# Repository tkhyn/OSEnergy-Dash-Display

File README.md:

# OSEnergy Dash Display

#####A 2" Dash Display for the VSR Alternator Regulator, and other OSEnergy complaint devices.

The OSEnergy Dashboard Display is a combination of hardware and software and designed to provide  information  of your battery and its associated charging sources.  Usable with any OSEnergy compliant device (such as the [VSR Alternator Regulator](http://arduinoalternatorregulator.blogspot.com/) ), this simple gauge will monitor the communications bus providing you with real-time updates of any active devices.

<br><br>
###How to Purchase and Install
The OSEnergy-Dash-Display source code has been proofed on the PUT NAME HERE AS WELL AS LINK open xxxx.  You can purchase a preassembled version complete with firmware installed here: link-here.

The raw display is sold by this person:  [https://www.tindie.com/stores/geraldjust/](https://www.tindie.com/stores/geraldjust/#store-section-products) 

The addaptor board gbr files are in this GitHub, or you can order some from  [OSHPARK](https://oshpark.com/shared_projects/Y1xcmnih) 

Firmware is in this Github, program the display using an FTDI cable.

Insert Photo of finished device

<br><br>
###Usage:

Once installed and connected, the Dash Display will monitor the CAN communications bus looking for battery information as well as any chargers associated with that battery.  Up to 4x different batteries may be monitored at one time, as well as up to 10x different charging sources.  When 1st powered up the display will show a  'Searching' message; as battery information is found it will change the display to reflect the battery as well as any charging source associated with that battery.

The PUT NAME HERE display hardware has 3 touch-pad buttons along the lower edge of the OLED display.  Pressing the LEFT button will cycle between battery information and its associated charging sources.  Pressing the RIGHT button will cycle between different batteries in your system.  After a period of inactivity the display may darken.  You can awaken the dash display by pressing the CENTER button

<br>
###Information displayed
####The following battery information may be displayed:
- Battery Name / ID number
- Battery Voltage, Current, Temperature
- Battery SOC

<br><br><br>
####The following Charging Source information may be displayed:
- Voltage at charging source
- Current being delivered by charging source
- Temperature of charging source
- % capability of charging source presently be utilized.
- Charging mode

Note that not all information may be available, depending on the capabilities of the associated device(s) installed in your system.  For example, if you only have a VSR Alternator Regulator installed battery SOC will not be shown.  To see Battery SOC you will need to install something which actually tracks SOC over the long term, such as a proper Battery Monitor or BMS.

<br><br>
####VSR Alternator Regulator Configuration Hints and notes:
- The  [VSR Alternator Regulator](http://arduinoalternatorregulator.blogspot.com/) needs to be configured to explicitly tell it its current shunt is located AT the battery by using the $CCN: command (Providing it is located at the battery).  Otherwise current will be recognized on the Alternator screen instead of the Battery screen.
- Generation 3 of the VSR Alternator Regulator does not supply power via the CAT-5 cable.  You will need to connect the external power wires on the display.  Generation 3B and beyond have the ability to provide power to the CAN CAT-5 cable directly, and no addition power wiring is needed.
- Update the VSR Alternator Regulator firmware  to version 1.3.1 or greater to maximize the capability of the Dash Display.

<br><br>
####Source code notes:
Download and compile using the Arduino IDE.  Make sure to install the ATmega64M1 CPU type as well as the AVR_CAN and RV-C libraries:

https://github.com/thomasonw/ATmegaxxM1-C1
https://github.com/thomasonw/avr_can
https://github.com/thomasonw/RV-C

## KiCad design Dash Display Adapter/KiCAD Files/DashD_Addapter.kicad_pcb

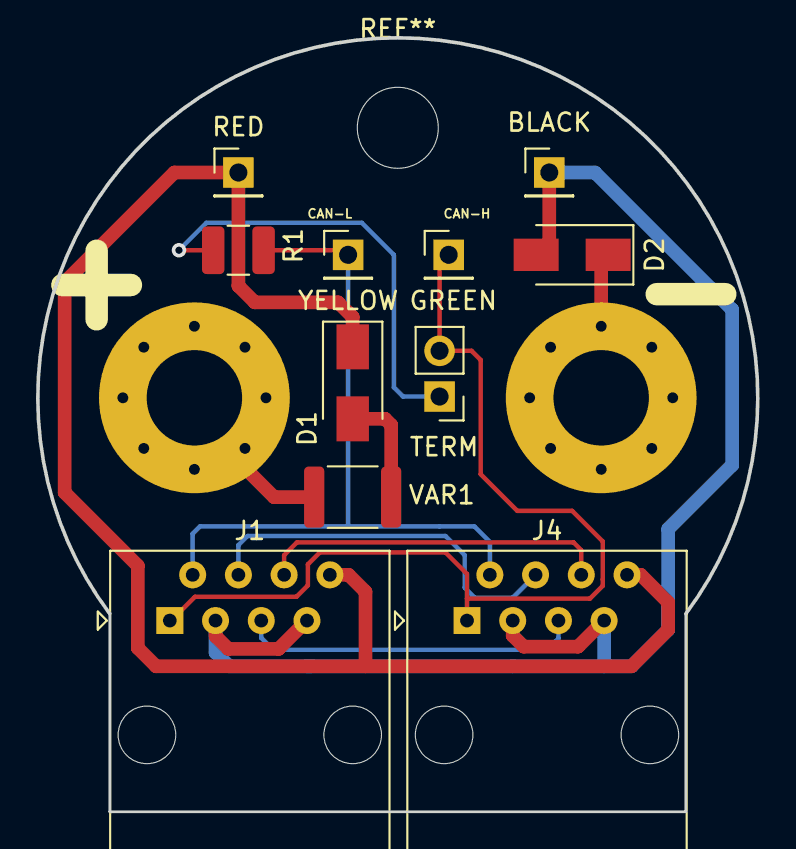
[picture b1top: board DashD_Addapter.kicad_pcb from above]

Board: 2 copper layers, 40.0 x 43.0 mm, 13 parts (0 on the bottom side), 11 nets.

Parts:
D1, D2: MRA4003T3G; D_SMA
J1, J4: CAN; RJ45_Amphenol_54602-x08_Horizontal
J2: GREEN; PinHeader_1x01_P2.54mm_Vertical
J3: YELLOW; PinHeader_1x01_P2.54mm_Vertical
J5: RED; PinHeader_1x01_P2.54mm_Vertical
J6: BLACK; PinHeader_1x01_P2.54mm_Vertical
J7: +; MountingHole_5.3mm_M5_Pad_Via
J8: -; MountingHole_5.3mm_M5_Pad_Via
J9: TERM; PinHeader_1x02_P2.54mm_Vertical
R1: 120; R_1210_3225Metric
VAR1: 350mA; Fuse_1812_4532Metric

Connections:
/+: J7.1, VAR1.2
/-: D2.1, J8.1
/CAN-H: J1.1, J2.1, J4.1, J9.2
/CAN-L: J1.2, J3.1, J4.2, R1.1
/CAN-V+: D1.1, J1.8, J4.8, J5.1
/CAN-V-: D2.2, J1.3, J1.7, J4.3, J4.7, J6.1
/XE: D1.2, VAR1.1
unnamed: J1.4, J4.4
unnamed: J1.5, J4.5
unnamed: J1.6, J4.6
unnamed: J9.1, R1.2

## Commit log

2018-07-16 Pre-release source and doc
    Pushing up functonal source and initial doc. Need to revise when new
    hardware is available
2018-07-16 Added example photos
2018-07-16 Removed Thumbs
    Sigh, how to keep them from being created in the 1st place!
2018-07-16 Nicer wording while searching
2018-07-17 Added proposed external CAN Rx IRQ port
2018-11-10 Adding daughter board GBR files
    Small daughter board to go on back of dask display unit - allows RJ45
    connectors
2018-12-17 Updated Adapter card
    Added TERM jumper.
2018-12-17 Small formating changes
    Working to improve readability.
2020-01-27 Remove thumbs.db file
